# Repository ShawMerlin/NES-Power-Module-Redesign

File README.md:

# NES Revival - Power-Module Redesign
Completely Redesigning the NES Power Module to Reduce Noise and EMI <br>
 <br>

6/21/2025
- I love this community, there has been a lot of folks reaching out.  I am doing well.  :)
- Zaxour, an amazing engineer and the person who helped me fix my design has his own version.
- I would highly recommend if you need a board to check his out.  - https://ko-fi.com/s/a42a9b282f
  
<br>
<br>
1/30/2025

I would like to thank the retro community for the love and support I have received over the years. <br>
At this time, I will no longer be offering these NES Boards on eBay or other channels. <br>
It's been a great couple of years but I must move on to other things in life. <br>
All of the Boards should have their Kicad files and Gerbers available on this Github. <br> <br>

It's not too bad ordering 5 of them pre-assembled from JLCPCB and then just sell the other 4 to get a free board.  :) <br>
I will not be able to provide support as well on these but I absolutely recommend the NES Help section on Dubesinhower Discord. <br>
https://x.com/dubesinhower?lang=en&mx=2 <br> <br>

There are a lot of amazing folks on that Discord Channel and in our community. <br>
Thank you for letting me be a part of it. <br>

-Merlin Shaw <br> <br> <br>

6/15/2024 <br>
Our first production run on NES Revival Classic RCA Editions have come in.  <br> <br>

6/4/2024 <br>
The NEW Revival RGBNES "Companion" Power Module production files have been released on this Github. <br> <br>

5/8/2024 <br>
I have my first RGB "Companion" 3.1c production boards run ready for eBay.  <br> <br>

4/5/2024 <br>
The RGBNES "Companion" Power Board v3.1b has passed it's prototype phase and I am ordering a production run. <br>
We are getting close to being able to release the gerber files for this design.  I just want to verify with the new order. <br> <br>

3/2/2024  <br>
GND Loop Issue Discovered on Older Boards and a Quick DIY Solution for it. <br>
https://github.com/ShawMerlin/NES-Power-Module-Redesign/blob/main/GND%20Loop%20Solution.md <br> <br>

2/13/2024 <br>
New Updates on the Rivial RGBNES 'Companion" Power Module <br>
https://github.com/ShawMerlin/NES-Power-Module-Redesign/blob/main/RGB%20-%20Genesis%209%20Pin%20Edition/readme.md <br> <br>

1/16/2024  <br>
I have a small sample of the new RGB "Companion" 3.0 Boards that are available  <br>
I will also update the classic design with the new features of the RGB Board and offer that one as well. <br>

https://github.com/ShawMerlin/NES-Power-Module-Redesign/tree/main/RGB%20-%20Genesis%209%20Pin%20Edition  <br>

<br> <br>

The original NES Power Module from the 80's is very noisy.  The Power Traces cross eachother and the ground home path is messy.
EMI was not a worry in 1985 but noise can impact picture and sound quality

Project is Open Sourced with a MIT License. It can be edited, changed and sold at your own discretion.  
Please link back here if this helps you with your own project.

=-=-=-Special Thanks to Project Guardian-=-=-=

# Goals with these new NES Power Modules
- Full Ground Plane that is uninterrupted and is free of traces and components.
- Power Traces that do not cross and have the GND plane below for a good return power signal.
- Have a specific NES Power Module for each use case (not try and pile everything into one board)

# NES Classic USB C Powered Module

# USB C Powered - NESRGB Companion Power Module with YPbPr "Component" Video

# NES Classic with Composite Out and Two Channel Mono Sound.

# NES RGB with Genesis 2 9 Pin Output

# Full uninterrupted ground plane on the back of the board.

# An easy to solder DIY Version of the Classic Composite RCA Edition.

# For the few that own the NES HDMI Board, this module will provide very easy solder points without the need of the LDO.

# Below is an example of the Orignal Power Module.  Notice how the power traces keep crossing eachother and other components. Folks really didn't consider EMI a lot back then and opted to just cover the entire board in a metal shroud.

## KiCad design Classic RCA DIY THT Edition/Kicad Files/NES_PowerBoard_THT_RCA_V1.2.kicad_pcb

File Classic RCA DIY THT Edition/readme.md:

# NES Revival PWR Board DIY Edition

A DIY NES Power Module for at home assembly that uses a LDO instead of a buck converter to get the voltage to 5V <br>
To View the Virtual BOM without downloading, click here - <a href="https://htmlpreview.github.io/?https://github.com/ShawMerlin/NES-Power-Module-Redesign/blob/main/Classic%20RCA%20DIY%20THT%20Edition/Virtual%20BOM%20-%20NES_PowerBoard_LDO_RCA_DIY_V3-0.html">Virtual BOM</a>

2/26/2024 - An issue was discovered with the pinout on the Q1 Transistor.  Version 3.1C was created to fix this pinout issue.  If Version 3.1b  <br>
has already been ordered, you can still use it but you have to rotate the transistor 90 degrees to put the legs in the right holes.  <br> 
Please reach out to me through email if you need help with this.  <br> <br>

2/18/2024 - Changed to a 4 layer PCB Board to help with coupling the front and back layer to the inner gnd layers.  This is only a few more
dollars for the PCB but is well worth it for noise reduction. <br> <br>

1/28/2024 - Moved the NES GND Connection pad closer to the 7805 <br> <br>  

1/20/2024 - Complete Redesign on Version 3.0 to get the 7805 back to where it is on the original Power Module. <br>
This will allow for the orignal Heatsink to be used or Regulator TSR2-2450 if no Heatsink is wanted. <br>
Extra Modifications for a Common Mode Choke and Bypass Capacitors on 5V Out to help reduce all Noise. <br>

 <br>
 I added a Low Cost tab in the BOM if noise is not as big of a concern.  Savings is about $5 from selecting these parts.  <br>

2/14/2023 - Minor changes to V1.3 including a correction in one of the capacitor values on the silkscreen and putting hot indicators <br>
          - Gerbers are now available that can be used at your favorite PCB Fab House. <br> <br>

 <br> <br>

Key Features on this board. <br>
- No SMD Parts, All THT and easy to solder. <br>
- L78S05CV for 2 Amps of Power <br>
- Power Indicator LED is optional with a Solder Jumper to enable. <br> <br>

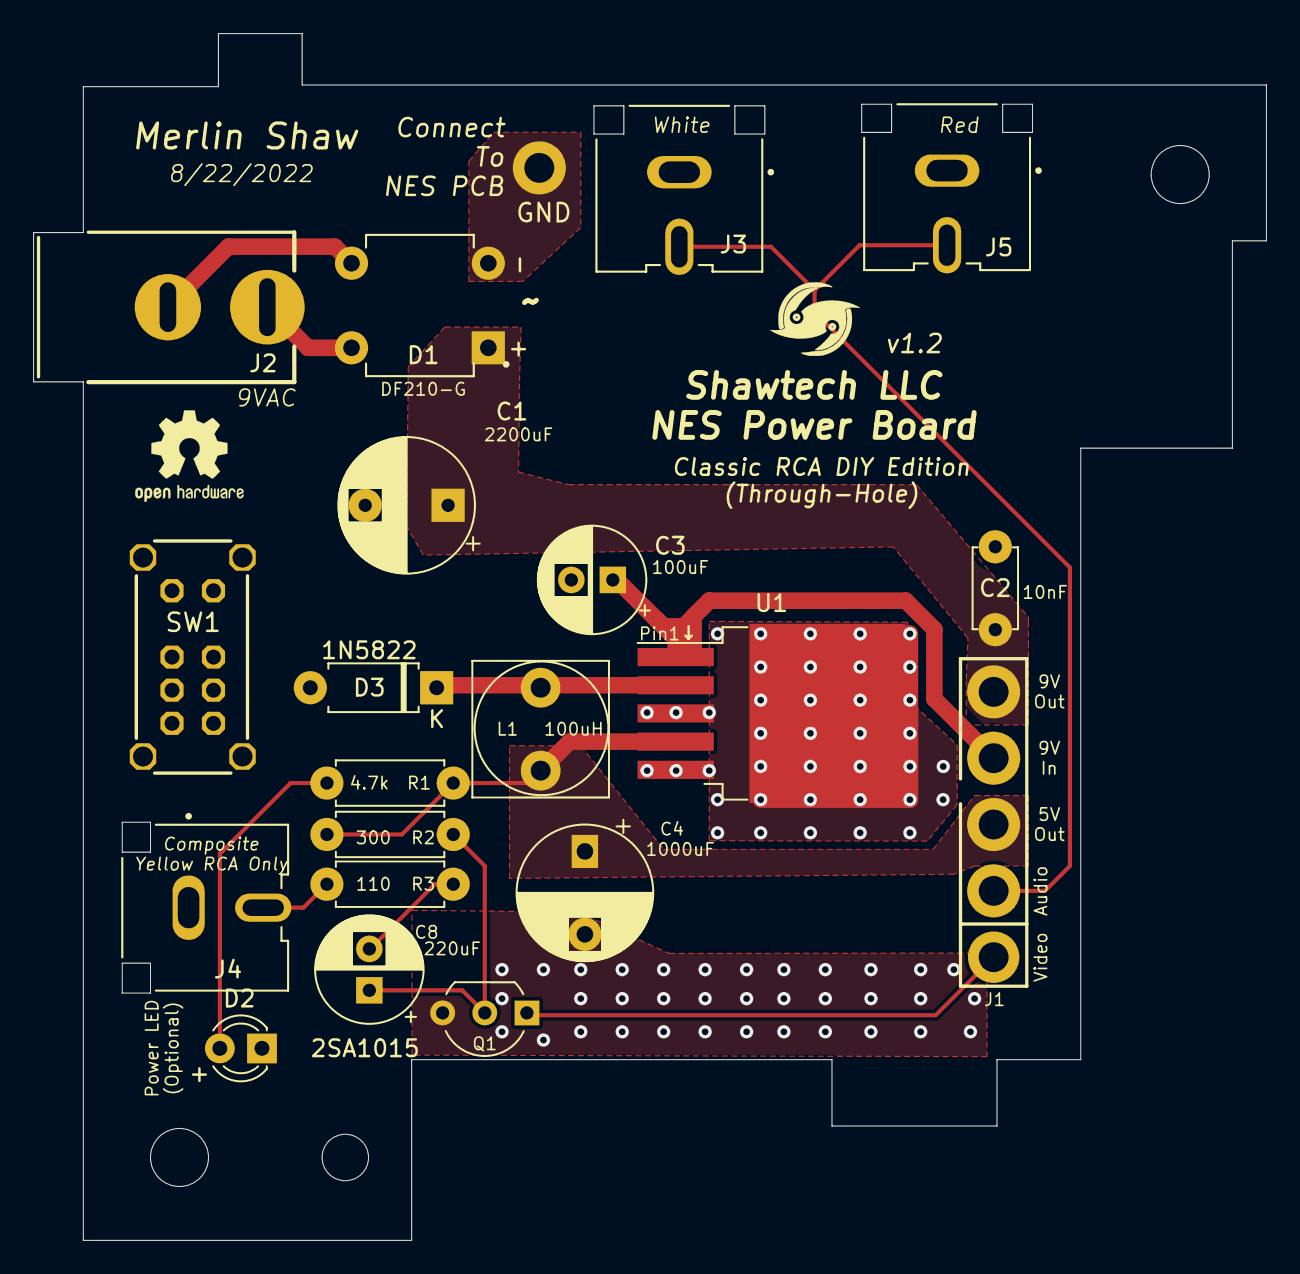
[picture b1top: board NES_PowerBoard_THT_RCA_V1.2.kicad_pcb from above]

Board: 2 copper layers, 74.3 x 72.8 mm, 21 parts (0 on the bottom side), 13 nets.

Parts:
C1: 2200uF 25V; CP_Radial_D8.0mm_P5.00mm
C2: 10nF; C_Disc_D4.7mm_W2.5mm_P5.00mm
C3: 100uF; CP_Radial_D6.3mm_P2.50mm
C4: 1000uF; CP_Radial_D8.0mm_P5.00mm
C8: 220uF; CP_Radial_D6.3mm_P2.50mm
D1: ${ALTIUM_VALUE}; DIP825
D2: Power LED; LED_D3.0mm_FlatTop
D3: DIODE; D_A-405_P7.62mm_Horizontal
GND: Wire Pad; WIREPAD-09-15
J1: Board Connector; RF BOARD CONNECTOR
J2: Barrel_Jack; PWR-JCK-ALT (PJ-037A{slash}B)
J3: White RCJ-52; CUI_RCJ-044
J4: Yellow RCJ-44; CUI_RCJ-044
J5: Red RCJ-042; CUI_RCJ-044
L1: 100uH; L_Radial_L8.0mm_W8.0mm_P5.00mm_Neosid_NE-CPB-07E
Q1: 2SA1015; TO-92_Inline_Wide
R1: 4.7k; R_Axial_DIN0207_L6.3mm_D2.5mm_P7.62mm_Horizontal
R2: 300; R_Axial_DIN0207_L6.3mm_D2.5mm_P7.62mm_Horizontal
R3: 110R; R_Axial_DIN0207_L6.3mm_D2.5mm_P7.62mm_Horizontal
SW1: DP3T; SW-DP3T (EG2319)
U1: LM2576D2TR4-5G; TO-263-5_TabPin3

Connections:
5V Out: C4.1, J1.3, L1.2, R1.2, R2.1, U1.4 (FB)
9VIn: C3.1, J1.4, U1.1 (VIN)
9VOut: C1.1, C2.1, D1.1 (V+), J1.5
Audio In: J1.2, J3.2 (Sleeve), J5.2 (Sleeve)
GND: C1.2, C2.2, C3.2, C4.2, D1.2 (V-), D2.1 (K), D3.2 (A), GND.1, J3.1 (Tip), J4.1 (Tip), J5.1 (Tip), Q1.3 (B), U1.3 (GND), U1.5 (ON/OFF)
unnamed: C8.1, Q1.2 (C), R2.2
unnamed: C8.2, R3.2
unnamed: D1.3 (AC), J2.2
unnamed: D1.4 (AC), J2.1
unnamed: D2.2 (A), R1.1
unnamed: D3.1 (K), L1.1, U1.2 (OUT)
Video In: J1.1, Q1.1 (E)
Video Out: J4.2 (Sleeve), R3.1

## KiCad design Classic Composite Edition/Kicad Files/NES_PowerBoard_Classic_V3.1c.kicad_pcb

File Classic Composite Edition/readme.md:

**1/15/2025 - Version 3.1c** <br>
- Updated a mistake in the BOM for the Digikey Part number to be correct on the Q1 Transistor. <br>
-  https://www.digikey.com/en/products/detail/evvo/2SA1015/22482092 <br> <br>
- Updated C12 to be 560pF, 1nF will work fine but 560pF produces a slightly sharper picture. <br>
-  https://www.digikey.com/en/products/detail/kemet/C0805C561J5GACAUTO/10642381 <br> <br>
- Updated Switching Regulator from Digikey to the H Variant in the BOM - 1/17/2025 <br>
-  https://www.digikey.com/en/products/detail/texas-instruments/TPS54202HDDCR/6026259 <br> <br>

**6/15/2024 - Version 3.1c** <br>
- It's been a long time coming but I wanted to make sure the RGBNES Versions were perfect. <br>
- This uses the exact same voltage regulator as the RGBNES Compantion Board. <br>
- GND Loop issue has been resolved. <br>
- 2 Audio Ports to give Duo Mono Sound. <br>
- Gerbers will be released for this later next week. <br>

**2/06/2024 3.0 Update** <br>
- I am in the process of testing our new 3.0 design with lots of great feedback from our community. <br>
- At this time, I do not recommend having any of the 2.0 boards built. <br>
- If you have already invested time/money into the older boards, Please contact me so we can work something out. <br>
- I have an official Statement on these new boards within a few weeks. <br>  <br>

**4/01/2023 2.1 Update**
- Create a Full Bridge Rectifier out of SMC Diodes for better heat dissapation into the PCB Board.
- Changed the 6.8uH Inductor to a 10uH inductor per the datasheet in order to reduce noise.
- Added an Input Inductor on the voltage regulator to reduce ringing on the circuit.
- Added a 1.9A Fuse for safety and including a tripped fuse LED indicator.
- Added more filtering caps on the 5v Output (47uF, 22uF, .1uF, 50pF)

**2/14/2023 2.0 Update**
- Upgraded the Full Bridge Rectifier to one that can do 5 Amps. The old version was getting pretty warm.
- Beefier DC Input Jack that can handle 5 Amps (old one could only do 2.5 amps)
- This Board has been tested pulling 3 Amps max without issue.
- Ground stitching over audio traces to help prevent any static and noise that would be coming from the Buck Converter.
- The Power LED turns on now when the Solder Bridge has been made. Meaning it can be disabled by removing the bridge.
- Most all parts are SMD now and made easy for an Assembly House like JLCPCB to build the PCB and Assemble for you.
- BOM and POS files are included that Assembly Houses will need.

**9/19/2022 Update**
- Version 1.8 - Increased the Ground Stitching around the Video Trace and added Ground Stitching to the Audio Trace.

I have uploaded the Gerbers for this board and also a Bill of Materials and Position File.
You can use both these .CSV files to have JLCPCB provide and Assemble the SMD parts for you.

# Picture Showcase!!

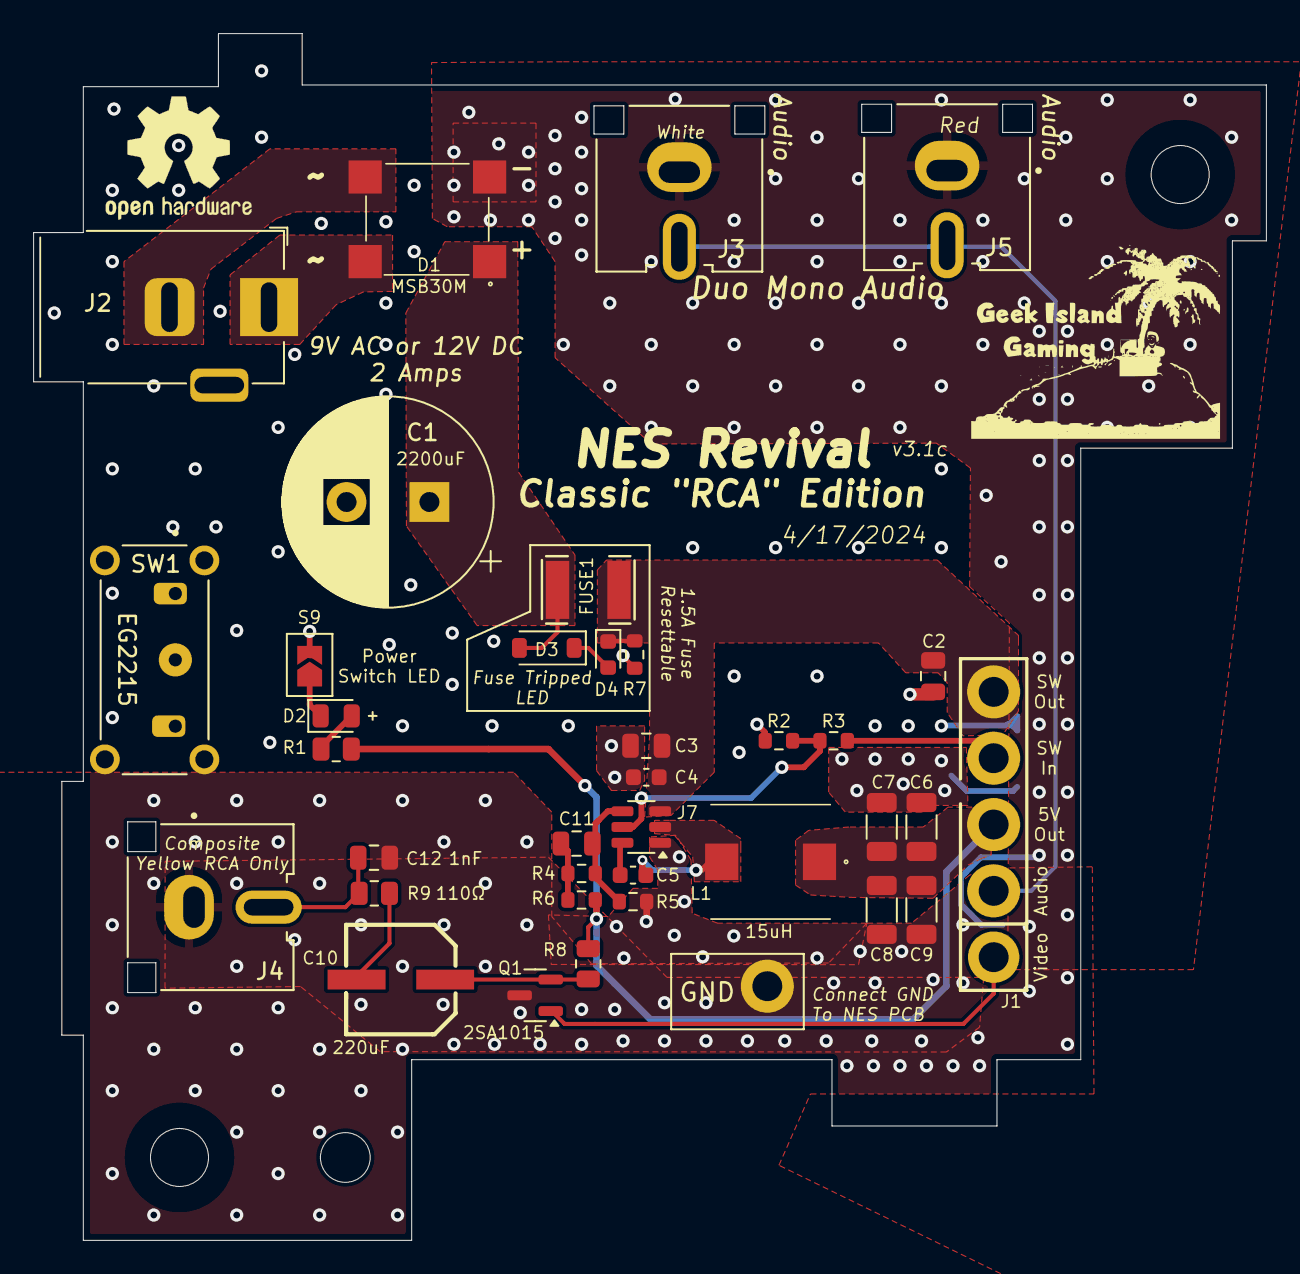
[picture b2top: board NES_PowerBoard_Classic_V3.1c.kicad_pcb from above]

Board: 4 copper layers, 74.3 x 72.8 mm, 37 parts (0 on the bottom side), 20 nets.

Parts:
C1: 2200uF 25V; CP_Radial_D12.5mm_P5.00mm
C2: 10nF; C_0805_2012Metric
C3: 10uF; C_0805_2012Metric
C4, C5: .1uF; C_0603_1608Metric
C6: 10nF; C_1206_3216Metric
C7, C8: 22uF; C_1206_3216Metric
C9: .1uF; C_1206_3216Metric
C10: 220uF; NESCAP
C11, C12: 75pF; C_0805_2012Metric
D1: MSB30M
D2: Power LED; LED_0805_2012Metric
D3: 1N4148W; D_SOD-123
D4: Power LED; LED_0603_1608Metric
FUSE1: F1812
GND: Wire Pad; GND
J1: Board Connector; RF BOARD CONNECTOR
J2: EJ503A; NES_EJ503A
J3, J4: White RCJ-; CUI_RCA
J5: Red RCJ-042; CUI_RCA
J7: TPS54202; SOT-23-6
JP1: Jump; SolderJumper-2_P1.3mm_Open_TrianglePad1.0x1.5mm
L1: 15uF; CLF7045T
Q1: 2SA1015; SOT-23
R1: 4,7K; R_0805_2012Metric
R2: 105K; R_0603_1608Metric
R3: 511K; R_0603_1608Metric
R4: 100K; R_0603_1608Metric
R5: 13.3K; R_0603_1608Metric
R6: 49.9; R_0603_1608Metric
R7: 4.7K; R_0603_1608Metric
R8: 300; R_0805_2012Metric
R9: 110R; R_0805_2012Metric
SW1: EG2215; SW_EG1224

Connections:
5V Out: C6.1, C7.1, C8.1, C9.1, J1.3, L1.1, R1.2, R6.2, R8.1
9VIn: J1.4, R3.2
9VOut: C1.1, D1.1, D3.2, FUSE1.1
9VOut2: C2.1, C3.1, C4.1, D4.1 (K), FUSE1.2, J1.5, J7.3, R7.1
A: J1.2, J3.2 (Sleeve), J5.2 (Sleeve)
AC: D1.2, J2.1
AC2: D1.4, J2.2
BOOT: C5.1, J7.6
EN: J7.5, R2.1, R3.1
FB: C11.1, J7.4, R4.1, R5.1
GND: C1.2, C2.2, C3.2, C4.2, C6.2, C7.2, C8.2, C9.2, C12.1, D1.3, GND.1, J3.1 (Tip), J4.1 (Tip), J5.1 (Tip), J7.1, JP1.2, Q1.3 (B), R2.2, R5.2, R7.2, SW1.S1, SW1.S2, SW1.S3, SW1.S4
GNDD: D2.1 (K), JP1.1
ICC4: C10.2, R9.2
MX: C11.2, R4.2, R6.1
unnamed: D2.2 (A), R1.1
RCA_Video: C12.2, J4.2 (Sleeve), R9.1
SW: C5.2, J7.2, L1.2
V5: D3.1, D4.2 (A)
Vid_In: C10.1, Q1.2 (C), R8.2
Video In: J1.1, Q1.1 (E)

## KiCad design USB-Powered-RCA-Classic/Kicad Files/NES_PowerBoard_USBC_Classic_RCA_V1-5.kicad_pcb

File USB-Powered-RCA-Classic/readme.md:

4/27/2024 - The Prototype of the USB C PD Power Board has been ordered and we should be testing it at the end of next week. <BR>
I do plan on offering these for sell when they have completed testing. <BR> <BR>

4/5/2024 - I added information to the older USB C Design.  I still do not recommend using this design. <BR>
I am close to ordering my first prototype for the USB C PD Board.  The Evaluation board I got to test this has worked great. <BR>
I hope to order within a few weeks, i'm just trying to save up for the order.  <BR> <BR>
Here is a sneak peak  ;)   <BR>

<BR>
<BR>
3/31/2024 - Please note that I am currently working on a USB C PD version that will be a lot more stable. <BR>
The USB C Standard allows for voltages between 4.75 and 5.75 volts.  The NES does not like voltages under or above 5.0-5.1 volts. <BR>
So it was kit or miss when it came to what USB C Brick was used. <BR> <BR>

With USB C PD, we will output a stable 9 - 12 volts and then use a voltage regulator to output a stable 5.07 volts. <BR>
This regulator has been tested and found to only have a 23mV peak to peak. <BR>
I plan to have this design ready for release in about 4 weeks. <BR> <BR>

<BR> <BR>

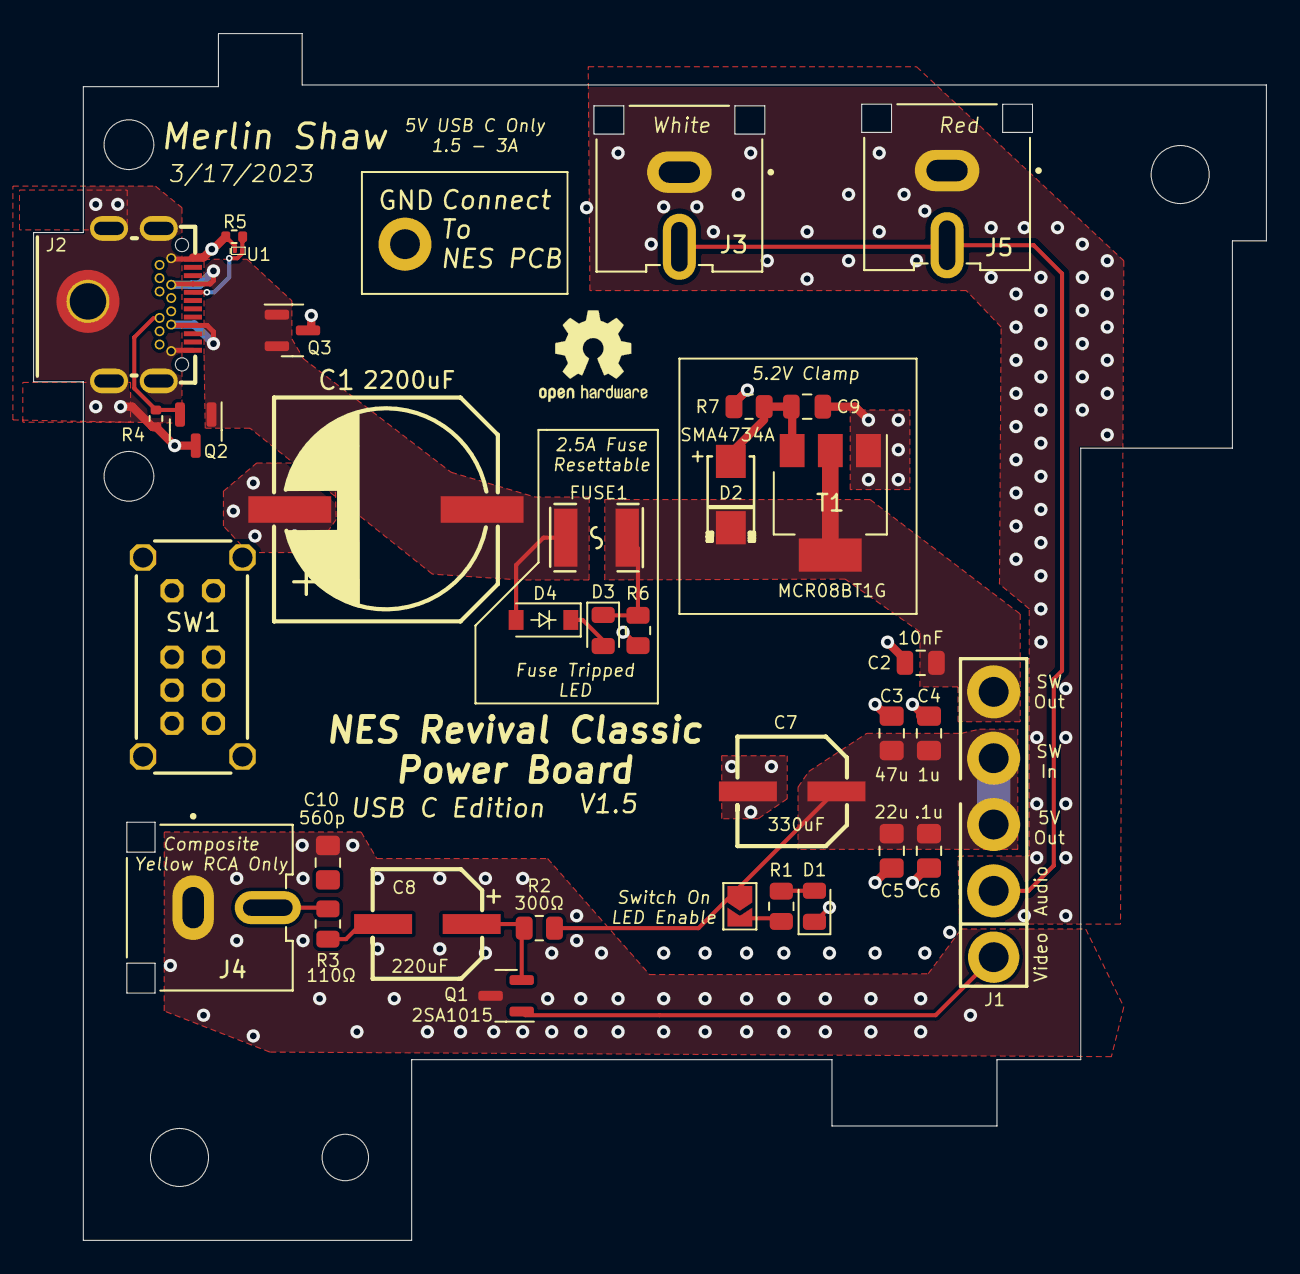
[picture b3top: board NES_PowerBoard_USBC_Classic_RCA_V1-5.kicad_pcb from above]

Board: 2 copper layers, 74.4 x 72.8 mm, 35 parts (0 on the bottom side), 15 nets.

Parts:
C1: CAP-SMD_BD12.5-L13.0-W13.0-RD
C2, C9: 10nF; C_0805_2012Metric
C3, C4, C5, C6: 22uf/25; C_0805_2012Metric_Pad1.18x1.45mm_HandSolder
C7, C8: 220uF; CAP-SMD_BD6.3-L6.5-W6.5-LS7.0-FD
C10: 560p; C_0805_2012Metric_Pad1.18x1.45mm_HandSolder
D1, D3: Power LED; LED_0805_2012Metric
D2: SMA_L4.2-W2.7-LS5.0-RD
D4: 1N4148W; D_SOD-123
FUSE1: F1812
GND: Wire Pad; WIREPAD-09-15
J1: Board Connector; RF BOARD CONNECTOR
J2: DX07S024XJ1R1100; USB-C-TH_DX07S024XJ1R1100-1
J3: White RCJ-52; CUI_RCJ-044
J4: Yellow RCJ-44; CUI_RCJ-044
J5: Red RCJ-042; CUI_RCJ-044
JP1: Jump; SolderJumper-2_P1.3mm_Open_TrianglePad1.0x1.5mm
Q1: 2SA1015; SOT-23
Q2, Q3: SP0502BAHTG; SOT-23
R1, R7: 680; R_0805_2012Metric
R2: 300; R_0805_2012Metric
R3: 110R; R_0805_2012Metric
R4, R5: 5.1k; R_0402_1005Metric
R6: 4.7K; R_0805_2012Metric
SW1: DP3T; SW-DP3T (EG2319)
T1: SOT-223-3_TabPin2
U1: DFN0603-D_L0.6-W0.3-P0.34-RD

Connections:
5V Out: C3.1, C4.1, C5.1, C6.1, C7.1, J1.3, J1.4, JP1.1, R2.1
9VOut: C1.1, D4.2, FUSE1.1, J2.A4, J2.A9, J2.B4, J2.B9, Q2.1 (E), Q3.1 (E), Q3.2 (C)
Audio In: J1.2, J3.2 (Sleeve), J5.2 (Sleeve)
CC1: J2.A5, R5.1, U1.2
CC2: J2.B5, Q2.2 (C), R4.1
GND: C1.2, C2.2, C3.2, C4.2, C5.2, C6.2, C7.2, C9.2, C10.2, D1.1 (K), GND.1, J2.0, J2.A1, J2.A12, J2.B1, J2.B12, J3.1 (Tip), J4.1 (Tip), J5.1 (Tip), Q1.3 (B), Q2.3 (B), Q3.3 (B), R4.2, R5.2, R6.2, R7.2, T1.1, U1.1
GTG: C9.1, D2.2, R7.1, T1.3
LED_IN: JP1.2, R1.2
unnamed: C8.1, Q1.2 (C), R2.2
unnamed: C8.2, R3.2
unnamed: D1.2 (A), R1.1
USB_Power_Out: C2.1, D2.1, D3.1 (K), FUSE1.2, J1.5, R6.1, T1.2
V5: D3.2 (A), D4.1
Video In: J1.1, Q1.1 (E)
Video Out: C10.1, J4.2 (Sleeve), R3.1

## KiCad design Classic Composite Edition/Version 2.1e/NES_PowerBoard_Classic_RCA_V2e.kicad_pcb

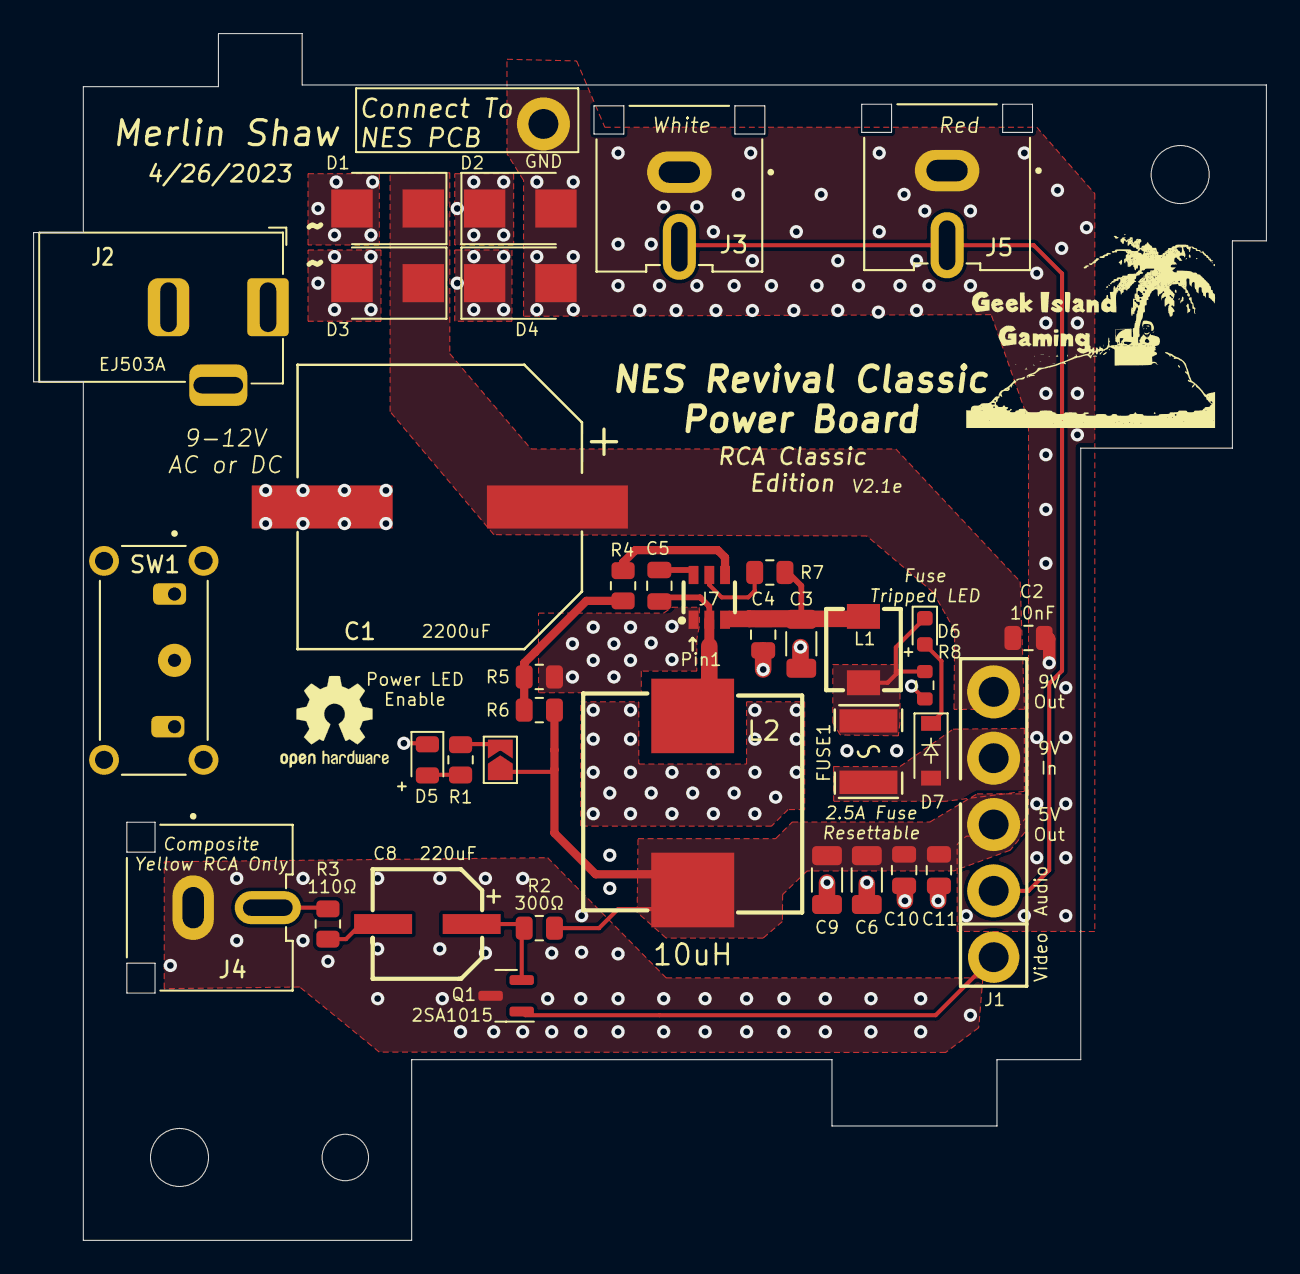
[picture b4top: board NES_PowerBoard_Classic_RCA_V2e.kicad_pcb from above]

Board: 2 copper layers, 74.4 x 72.8 mm, 38 parts (0 on the bottom side), 21 nets.

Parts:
C1: CAP-SMD_BD16.0-L17.0-W17.0-FD-LS18.0
C2: 10nF; C_0805_2012Metric
C3, C6: 22uf/25; C_1206_3216Metric
C4, C10: .1uF/25; C_0805_2012Metric
C5: 1uF; C_0805_2012Metric
C8: 220uF; CAP-SMD_BD6.3-L6.5-W6.5-LS7.0-FD
C9: 47uF; C_1206_3216Metric
C11: 50pF; C_0805_2012Metric
D1, D2, D3, D4: SD560B; D_SMB
D5: Power LED; LED_0805_2012Metric
D6: Power LED; LED_0603_1608Metric
D7: 1N4148W; D_SOD-123
FUSE1: SMD1812P150TF/16; F1812
GND: Wire Pad; WIREPAD-09-15
J1: Board Connector; RF BOARD CONNECTOR
J2: DC-005-5A-2.5; BarrelJack_Horizontal
J3: White RCJ-52; CUI_RCJ-044
J4: Yellow RCJ-44; CUI_RCJ-044
J5: Red RCJ-042; CUI_RCJ-044
J7: SOT-23-6_L2.9-W1.6-P0.95-LS2.8-BR
L1: IND-SMD_L4.9-W4.5
L2: IND-SMD_L13.0-W13.0
Q1: 2SA1015; SOT-23
R1: 2.2k; R_0805_2012Metric
R2: 300; R_0805_2012Metric
R3: 110R; R_0805_2012Metric
R4: 10k; R_0805_2012Metric
R5: 7.68k; R_0805_2012Metric
R6: 40.2k; R_0805_2012Metric
R7: 100K; R_0805_2012Metric
R8: 2.2k; R_0603_1608Metric
RJV-EXT1: Resistor; SolderJumper-2_P1.3mm_Open_TrianglePad1.0x1.5mm
SW1: EG2215; SW_EG1224

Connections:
5V Out: C6.1, C9.1, C10.1, C11.1, J1.3, L2.2, R2.1, R6.2, RJV-EXT1.1
9VIn: D7.2, FUSE1.2, J1.4
9VOut: C1.1, C2.1, D1.1, D3.1, J1.5
9V_Int: D6.1 (K), FUSE1.1, L1.2, R8.1
9V_Ont: C3.1, C4.1, J7.3, L1.1, R7.2
/AC+: D3.2, D4.1, J2.1
/AC-: D1.2, D2.1, J2.2
Audio In: J1.2, J3.2 (Sleeve), J5.2 (Sleeve)
EN: J7.5, R7.1
GND: C1.2, C2.2, C3.2, C4.2, C6.2, C9.2, C10.2, C11.2, D2.2, D4.2, D5.1 (K), GND.1, J3.1 (Tip), J4.1 (Tip), J5.1 (Tip), J7.1, Q1.3 (B), R5.2, R8.2, SW1.S1, SW1.S2, SW1.S3, SW1.S4
LED_On: R1.2, RJV-EXT1.2
unnamed: C5.1, J7.6
unnamed: C8.1, Q1.2 (C), R2.2
unnamed: C8.2, R3.2
unnamed: D5.2 (A), R1.1
unnamed: J7.4, R4.1
unnamed: R4.2, R5.1, R6.1
SW: C5.2, J7.2, L2.1
V5: D6.2 (A), D7.1
Video In: J1.1, Q1.1 (E)
Video Out: J4.2 (Sleeve), R3.1

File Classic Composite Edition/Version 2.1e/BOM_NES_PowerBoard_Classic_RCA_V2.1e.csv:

Comment,Designator,SMD Footprints,LCSC,Mouser
2200uF,C1,CAP-SMD,C249624,
.01uF,C2,C_0805_2012Metric,C1710,
22uF,"C3,C6",C_1206_3216Metric,C12891,
.1uF,"C4,C10",C_0805_2012Metric,C49678,
1uF,C5,C_0805_2012Metric,C28323,
220uF,C8,CAP-SMD_BD6.3-L6.5-W6.5-LS7.0-FD,C259967,
47uF,C9,C_1206_3216Metric,C426659,
50pF,C11,C_0805_2012Metric,C1823,
SD560B,"D1,D2,D3,D4",D_SMB,C260348,
Green_LED,D5,LED_0805_2012Metric,C2297,
Red_LED,D6,LED_0603_1608Metric,C84263,
1N4148W,D7,D_SOD-123,C81598,
SMD1812P150TF/16,FUSE1,1812,C20810,
DC-005-5A-2.5,J2,BarrelJack_Horizontal,C381115,
BL8033,J7,SOT-23-6L,C160717,
JSHC0420-R56M,L1,IND-SMD_L4.9-W4.5,C386774,
SLB1360P100MTT,L2,IND-SMD_L13.0-W13.0,C397796,
2SA1015,Q1,Package_TO_SOT_SMD:SOT-23,C181170,
2K,R1,R_0805_2012Metric,C17520,
300R,R2,R_0805_2012Metric,C17617,
110R,R3,R_0805_2012Metric,C246031,
10K,R4,R_0805_2012Metric,C17414,
7.68k,R5,R_0805_2012Metric,C30041,
40.2k,R6,R_0805_2012Metric,C17678,
100K,R7,R_0805_2012Metric,C149504,
2K,R8,R_0603_1608Metric,C4190,
,,,,
,,,,
,,,,
Comment,Designator,Through Hole FootPrints,LCSC,Mouser
Red RCA,J5,Right Audio - Red RCA Jack,,"RCJ-042	"
White RCA,J3,Left Audio - White RCA Jack,,"RCJ-043	"
Yellow RCA,J4,Video Out Yellow RCA Jack,,"RCJ-044	"

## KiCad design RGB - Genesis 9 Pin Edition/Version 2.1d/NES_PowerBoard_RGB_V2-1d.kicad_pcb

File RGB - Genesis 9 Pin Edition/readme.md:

# NES Revival RGBNES "Companion" Power Module.   <br>

1/15/2024 <br>
- over 100 of these 3.1c boards have been sent out on my eBay store.
- A few installation errors but we have not seen any buck converters giving up the smoke!
- Corrected a mistake in the Digikey part number of the Q1 Transistor, the JLCPCB number was correct.
- We are recommending a 560pF instead of the 1nF capacitor on C12, this provides a slightly crisper image.
- Added the H variant of the switching regulator to the Digikey BOM.

6/4/2024 <br>
- Production files have been released for version 3.1c <br> <br>

5/8/2024 - Version 3.1c is production ready, Gerbers will be released this week. <br>
I have a full analsyis with aid from Zaxour to show peformance levels for these boards. <br> <br>

<br> <br>
3/1/2024 - Testing of the new Design 3.0b is going well.  <br>
- We have moved to a 4 layer board to increase the coupling of the switching components to the inner GND layers. <br>
- The Switch input is only used now to power the enable pin on the Buck Converter.  The Input power comes directly from the board itself. <br>
- GND to NES Connector has been moved closer to the Voltage Regulator to reduce the GND Loop area. <br>
- Inductor has been moved further away from the interconnect pins and more bypass capacitors have been added to help reduce noise. <br>
- I plan on doing a more indepth analsys of this design vs the older design and releasing the results. <br>
- All Kicad files and Gerber files will be released once testing is completed. <br>

 <br>  <br>
2/13/2024 - Production Boards have been ordered. <br>
- Testing has been going great!!  I have now ordered my first production run. <br>
- With some help from this great community, I have made improvments to the design. <br>
- I plan on releasing a full breakdown of these new boards and some words on older designs. <br>
- Open Source Files will be released once the Production Boards are verified <br> <br>

1/16/2024 - Features of the 3.0 Boards  <br>
- Stable and clean 5.06 volts at a 1.5A load.  (7.5 watts) <br>
- Tested for 48 hours at a 1.8A load (9 watts) <br>
- Peaks of 2A are fine, but it's pushing the components pretty hard. <br>
- 1.5A Resettable Fuse on 9V input for board protection. (13.5 watts) <br>
- The LCSC Chinese Voltage Regulator has been replaced with a TE Connectivity IC. (TPS54202) <br>
- The Full Bridge Rectifier is a Diode Incorporate part. (MSB30M) <br>
- All Parts can be obtained from Digi-Key/Mouser. <br>
- Gerbers and Kicad files will be released once testing burn-in is complete. <br>
- I also plan on offering these again on my eBay account once i'm done with testing. <br>

<br> <br>
4/30/2023 - <br> <br>
When connecting the RGBNES to this PWR Module, do not use the main RGB Headers on the RGBNES. <br>
- The Gen2 Cables have circuits in them to treat the RGB Signal.  The main RGB Headers on the RGBNES are also treating the RGB Signal. <br>
- If these header points are used, the picture will be a lot darker as a result. <br>
- There are other points on the RGBNES that can be used that have the RAW RGB Data before all the processing. <br>
- Use of the RAW RGB points will allow the picture's brightness to be accurate and good. <br>
- Reference these pins [HERE](https://github.com/ShawMerlin/NES-Power-Module-Redesign/blob/main/RGB%20-%20Genesis%209%20Pin%20Edition/Features%20and%20Components.md) <br>

   <br>

4/03/2023 - Newer features of the 2.1 Boards <br>
- Using JST 2.0 PH Connectors now so the wires are not so microscopic. <br>
- Updated the Audio Selection Switch to also control Audio Output on the Gen2 Port. <br>
- Added the Internal Componsite Circuit so now this board can be fully used without a RGBNES Installed. <br>
- Video Selection switch will now control whether Int or Ext Video is outputted on the RCA Jack. <br>
- If Dual Mono Audio is desired, a simple RCA Y Splitter cable can be used on the Red RCA Jack. <br>

3/13/2023 <br>
Gerbers, BOM and POS (JLCPCB Assembly) have been released and are on this github page. <br>

Key Features on this board.
- Switching Voltage Regulator.  This outputs a lot less heat and a stable 5V Supply.
- Seperate Ground Plane from the 5V Regulator and the RGB Traces.  2 Grounding points on the Board. 
- Physical cut outs in the PCB board to help shield against any EMI from the regulator.
- Switch for selection of Internal Audio or External Audio (if you have your own Audio Circuit)
- Switch for Selection of the Multi-Function RCA Jack to be Left (mono Audio) or Composite from the RGB Board.
- 3 Way Side Switch that can be wired into the Palette Selection on the RGB Board - 
- Gen2 Output is compatible with the Scart Adapters, HDRetrovision Cable, OSSC and the Retrotink.  
- The RGBNES offers Raw RGB Output pads as the Gen2 Cables will add 75 ohm resistors. Check instructions for more details.

Click here for a list of the features this board offers - [Link](https://github.com/ShawMerlin/NES-Power-Module-Redesign/blob/main/RGB%20-%20Genesis%209%20Pin%20Edition/Features%20and%20Components.md)

Click here for Instructions on how to install this Power Module - [Link](https://github.com/ShawMerlin/NES-Power-Module-Redesign/blob/main/Install_Instructions.md)

(RGBNES Required for the Gen2 Port on this No Cut Mod Board, Normal Componsite and Audio will still work without it.) <br>

Shoutout to Long Island Retro Gaming for the screenshot!! - https://www.youtube.com/@LIRetroGaming

<br> <br>
Update History <br>

3/20/2023 - Feedback from testers has been excellent.  I have received great feedback which is being done in the next revision.  <br>  <br>
Revisions for V2.1
- Removed the ability to use the multifuction port as an Audio Port.  It is now Video Componsite Only.  <br>
- Added the internal Composite circuitry back to the Power Board and made the seldctor switch, Int Video and Ext Video.  <br>

3/2/2023 - Testing is going good.  I am sending engineering samples to various testers in order to get feedback. <br>

Final Revision for V2.0 that brings some quality of life updates. <br>
- Moved the Optional Power LED to a more central location.  <br>
- Changed the Pitch from JST XH 1.5mm to JST PH 2.0mm to make it a lot easier to solder without bridges.  <br>
- Rotated JST Connector so now a right angle one can be used.  <br>
- Gen2 Audio Output now is controlled by the Ext/Int Audio Switch. <br>
- Rotated the Palette Switch outputs for easier access. <br> <br>

2/28/2023 - Boards have arrived and are assembled.  I couldn't find my Gen2 9 Pin to SCART cable so I had to order a new one.  <br>
It sohuld arrive today and after testing is complete.  All files will be released on this github. <br>

2/1/2023 - Getting back on the horse!!  I have Version 1.9 completed and ordered. I should be able to test within a couple of weeks.
This new version has slide switches instead of header jumpers and I have also changed the pinout on the 7 pin connector to match the color of wires.

9/12/2022 - I have made a couple of changes to the RGB Board, I have moved the 9 pin Genesis Connector closer and fixed part of the audio circuit.
The Gerber files have been taken down until we get this new one tested.

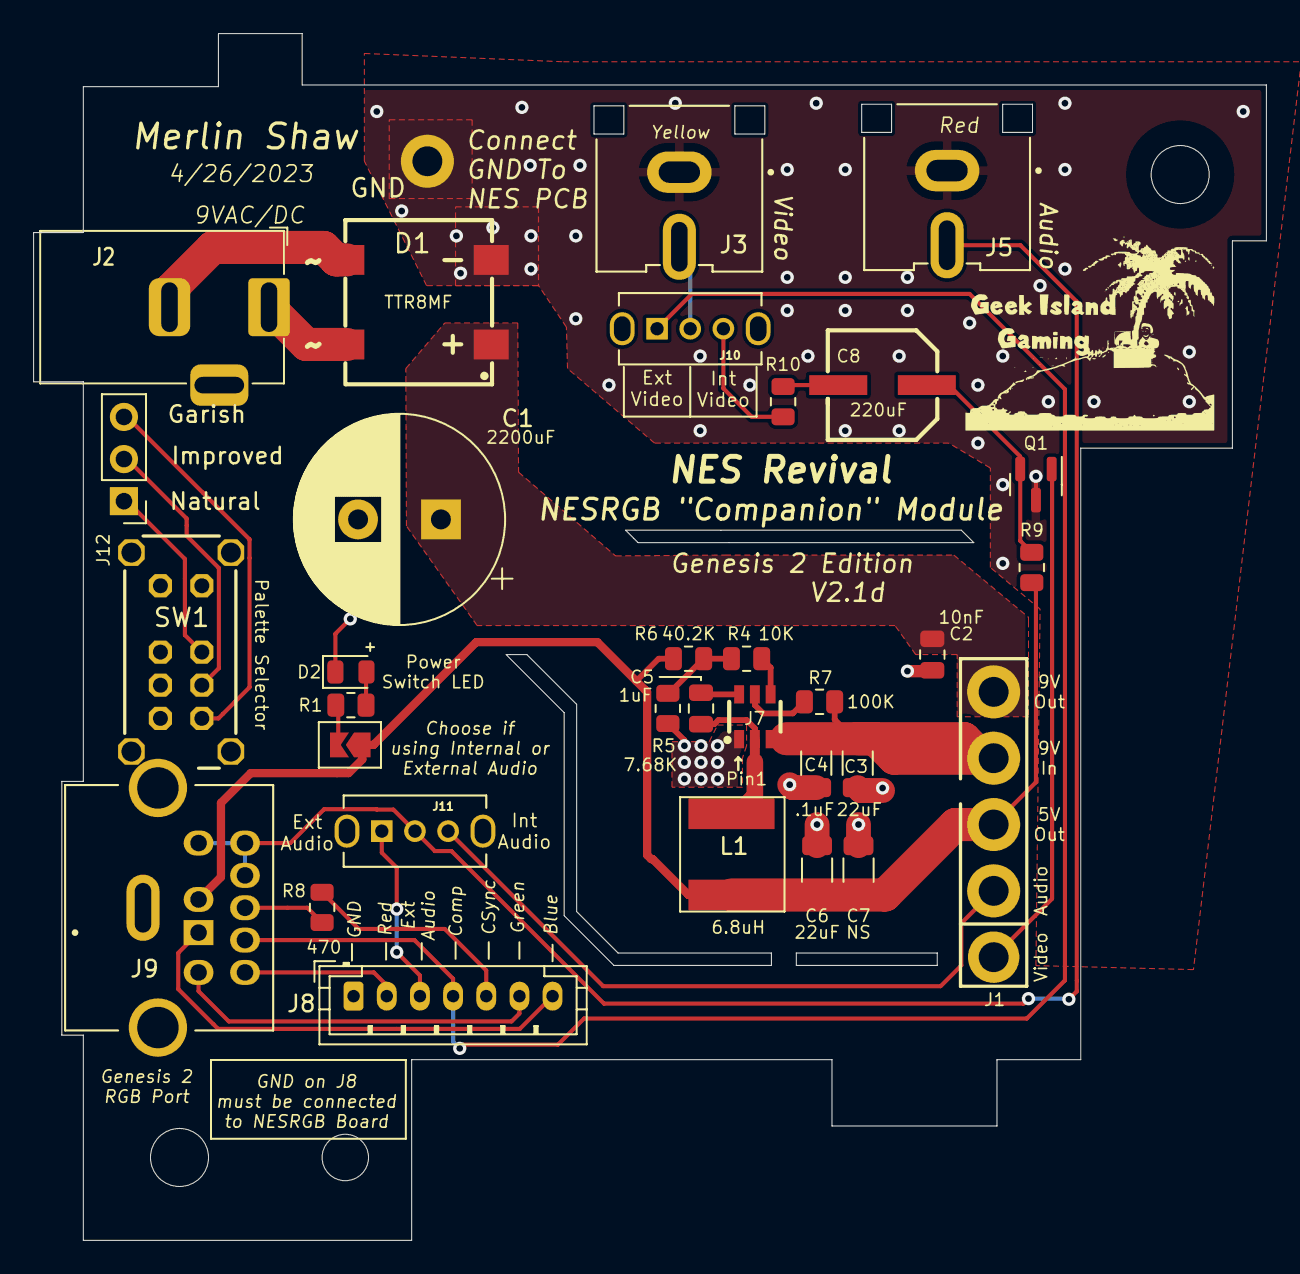
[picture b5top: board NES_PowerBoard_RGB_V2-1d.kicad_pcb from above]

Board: 2 copper layers, 74.3 x 72.8 mm, 33 parts (0 on the bottom side), 31 nets.

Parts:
C1: 2200uF 25V; CP_Radial_D12.5mm_P5.00mm
C2: 10nF; C_0805_2012Metric
C3, C6, C7: 22uf/25; C_1206_3216Metric
C4: .1uF; C_1206_3216Metric
C5: 1uF; C_0805_2012Metric
C8: 220uF; CAP-SMD_BD6.3-L6.5-W6.5-LS7.0-FD
D1: AC; DIO-BG-TH_TTF
D2: Power LED; LED_0805_2012Metric
GND: Wire Pad; WIREPAD-09-15
J1: Board Connector; RF BOARD CONNECTOR
J2: DC-005-5A-2.5; BarrelJack_Horizontal
J3: White RCJ-; CUI_RCJ-044
J5: Red RCJ-042; CUI_RCJ-044
J7: SOT-23-6_L2.9-W1.6-P0.95-LS2.8-BR
J8: ${ALTIUM_VALUE}; JST_PH_B7B-PH-K_1x07_P2.00mm_Vertical
J9: MD-90SM; CUI_MD-90SM
J10: Conn_01x03; SW_OS102011MS2QN1
J11: DP3T; SW_OS102011MS2QN1
J12: ${ALTIUM_VALUE}; PinHeader_1x04_P2.54mm_Vertical
L1: 6.8uH; Inductor-L_6.3x6.3_H3
Q1: SOT-23
R1: 680; R_0805_2012Metric
R4: 10k; R_0805_2012Metric
R5: 7.68k; R_0805_2012Metric
R6: 40.2k; R_0805_2012Metric
R7: 100K; R_0805_2012Metric
R8: 470; R_0805_2012Metric
R9: 300; R_0805_2012Metric
R10: 110R; R_0805_2012Metric
RJV-EXT1: Resistor; SolderJumper-2_P1.3mm_Open_TrianglePad1.0x1.5mm
SW1: DP3T; SW-DP3T (EG2319)

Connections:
2i2: C8.1, Q1.2 (C), R9.2
2t2: C8.2, R10.2
5V Out: C6.1, C7.1, J1.3, J9.2, L1.2, R6.2, R9.1, RJV-EXT1.1
9VIn: C3.1, C4.1, J1.4, J7.3, R7.2
9VOut: C1.1, C2.1, D1.1, J1.5
A: J1.2, J11.3
AC: D1.4, J2.1
AC2: D1.3, J2.2
Aud: J8.3 (Chroma), J11.1
Audio In: J5.2 (Sleeve), J9.6, J9.8, J9.9, J11.2
Blue: J8.7 (Green), J9.1
CSync: J8.5 (Composite), R8.2
Csync2: J9.5, R8.1
EN: J7.5, R7.1
GND: C1.2, C2.2, C3.2, C4.2, C6.2, C7.2, D1.2, D2.1 (K), GND.1, J3.1 (Tip), J5.1 (Tip), J7.1, Q1.3 (B), R5.2
Gnd2: J8.1 (Audio), J9.S1 (SHIELD), J9.S2 (SHIELD), J9.S3 (SHIELD), SW1.5, SW1.MH
Green: J8.6 (Blue), J9.3
Int_Vid: J10.3, R10.1
LED_In: R1.2, RJV-EXT1.2
MultiFunction: J3.2 (Sleeve), J10.2
unnamed: C5.1, J7.6
unnamed: D2.2 (A), R1.1
unnamed: J7.4, R4.1
unnamed: R4.2, R5.1, R6.1
unnamed: J12.1, SW1.6
unnamed: J12.2, SW1.7
unnamed: J12.3, SW1.8
Red: J8.2 (GND), J9.7
SW: C5.2, J7.2, L1.1
Video In: J1.1, Q1.1 (E)
Video Out: J8.4 (Luma), J9.4, J10.1

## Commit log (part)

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2023-02-14 Create Notes
2023-03-13 Create Features and Components
2023-04-22 Test
    Testing Permissions, Remove in next Push.
2025-01-31 Switch for Classic version is an EG2215
